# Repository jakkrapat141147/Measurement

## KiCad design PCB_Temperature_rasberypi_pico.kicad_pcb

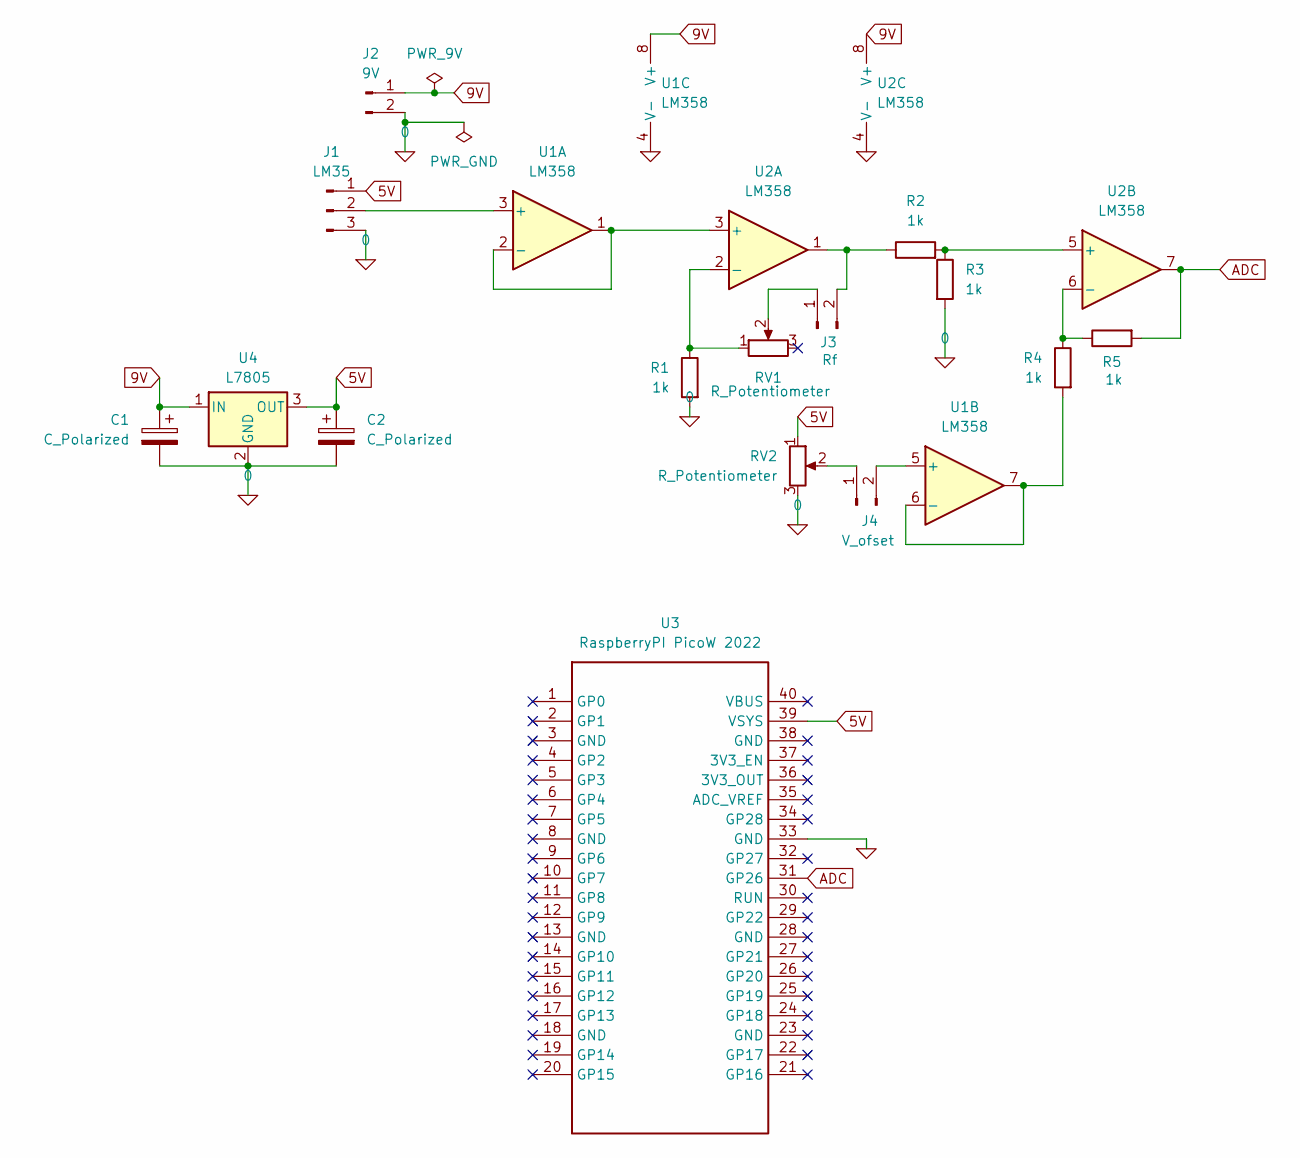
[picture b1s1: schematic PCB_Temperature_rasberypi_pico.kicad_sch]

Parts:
C1, C2: C_Polarized; CP_Radial_D5.0mm_P2.50mm
J1: LM35; PinHeader_1x03_P2.54mm_Vertical
J2: 9V; PinHeader_1x02_P2.54mm_Vertical
J3: Rf; PinHeader_1x02_P2.54mm_Vertical
J4: V_ofset; PinHeader_1x02_P2.54mm_Vertical
R1, R2, R3, R4, R5: 1k; R_0603_1608Metric_Pad0.98x0.95mm_HandSolder
RV1, RV2: R_Potentiometer; Potentiometer_Bourns_3296X_Horizontal
U1: LM358
U2: LM358; DIP-8_W7.62mm
U3: RaspberryPI PicoW 2022; RASPERRYPI_PICOW_2022
U4: L7805; TO-220-3_Horizontal_TabDown

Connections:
0: C1.2, C2.2, J1.3, J2.2, R1.2, R3.2, RV2.3, U1.4 (V-), U2.4 (V-), U3.33 (GND), U4.2 (GND)
5V: C2.1, J1.1, RV2.1, U3.39 (VSYS), U4.3 (OUT)
9V: C1.1, J2.1, U1.8 (V+), U2.8 (V+), U4.1 (IN)
ADC: R5.2, U2.7, U3.31 (GP26)
unnamed: J1.2, U1.3 (+)
unnamed: J3.1, RV1.2
unnamed: J3.2, R2.1, U2.1
unnamed: J4.1, RV2.2
unnamed: J4.2, U1.5 (+)
unnamed: U1.1, U1.2 (-), U2.3 (+)
unnamed: R4.2, U1.6 (-), U1.7
unnamed: R1.1, RV1.1, U2.2 (-)
unnamed: R2.2, R3.1, U2.5 (+)
unnamed: R4.1, R5.1, U2.6 (-)

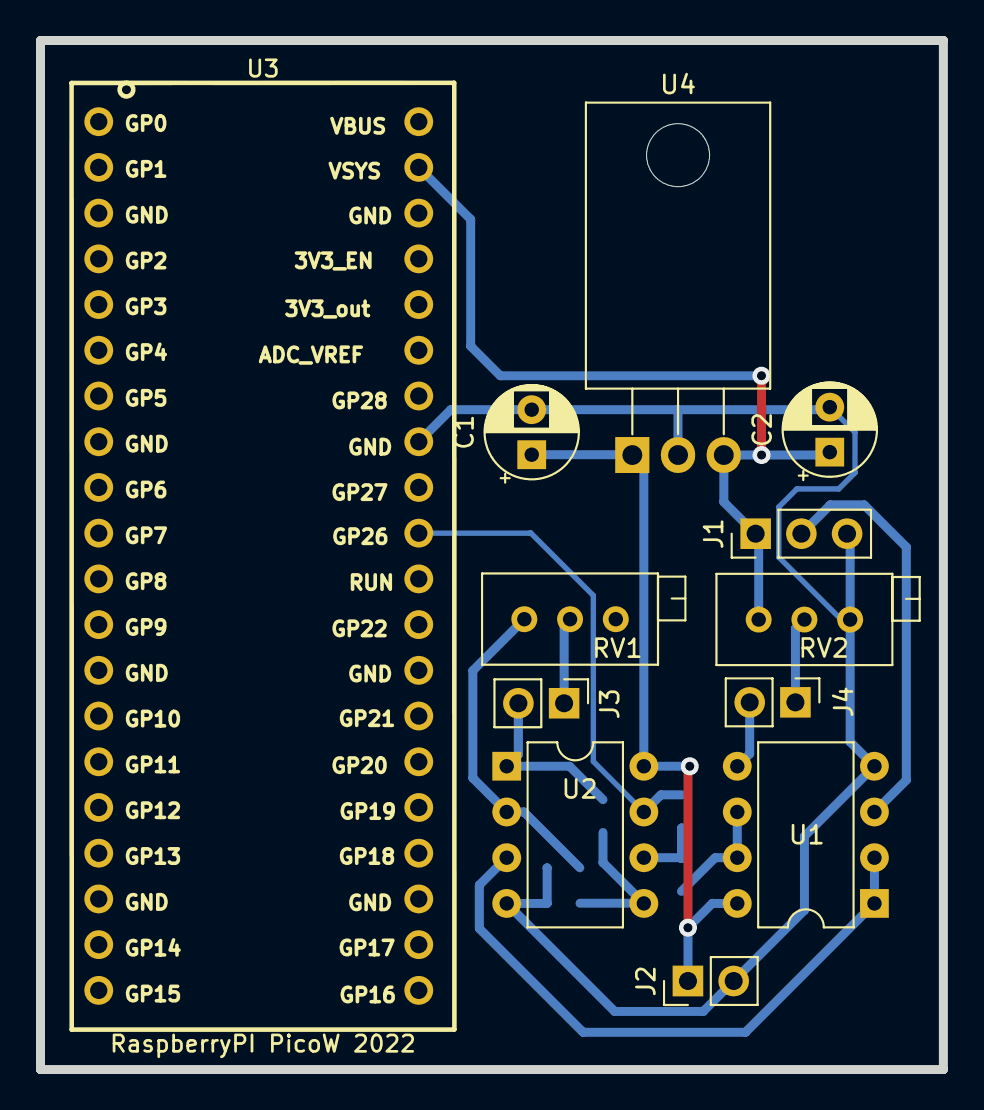
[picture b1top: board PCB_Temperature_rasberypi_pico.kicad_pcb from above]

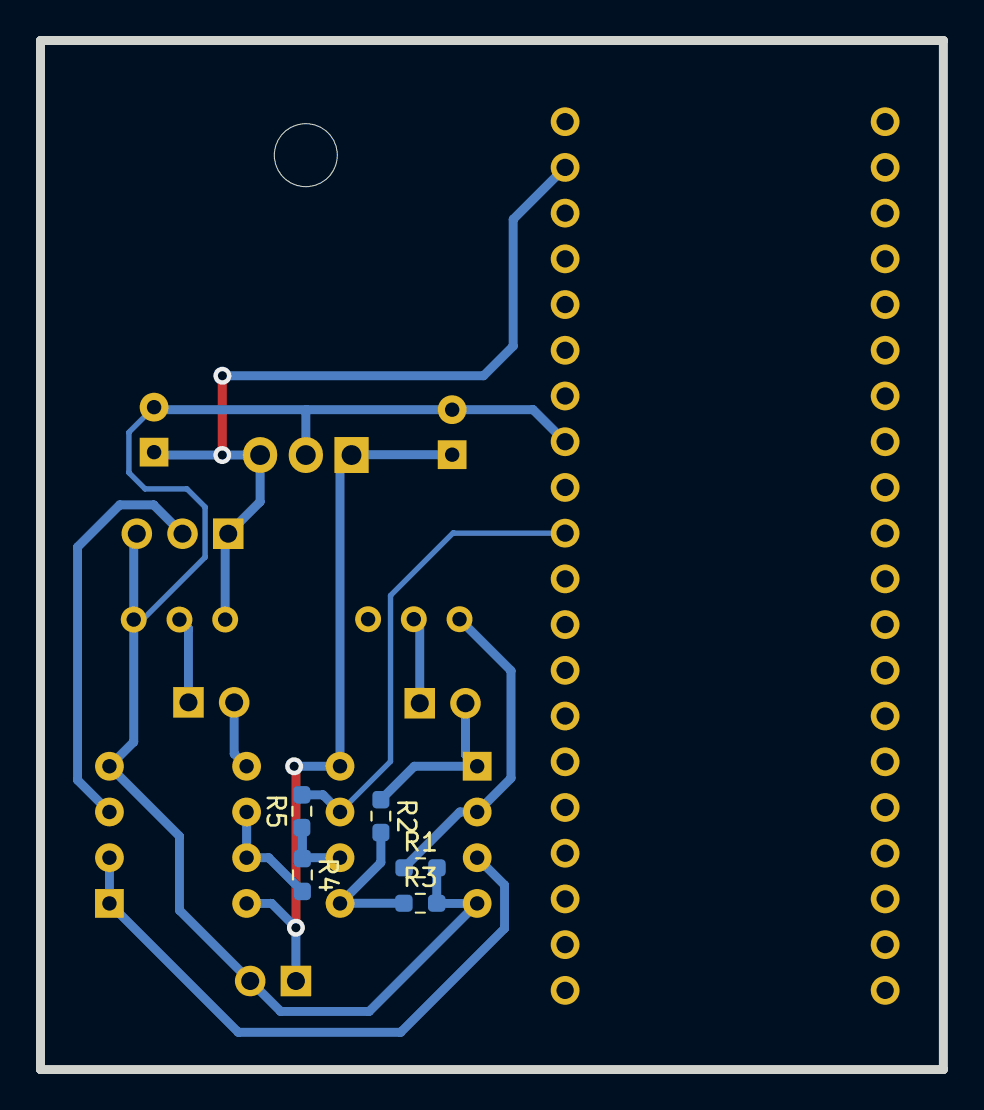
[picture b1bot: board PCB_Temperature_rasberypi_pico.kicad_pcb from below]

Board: 2 copper layers, 50.2 x 57.2 mm, 17 parts (5 on the bottom side), 14 nets.
